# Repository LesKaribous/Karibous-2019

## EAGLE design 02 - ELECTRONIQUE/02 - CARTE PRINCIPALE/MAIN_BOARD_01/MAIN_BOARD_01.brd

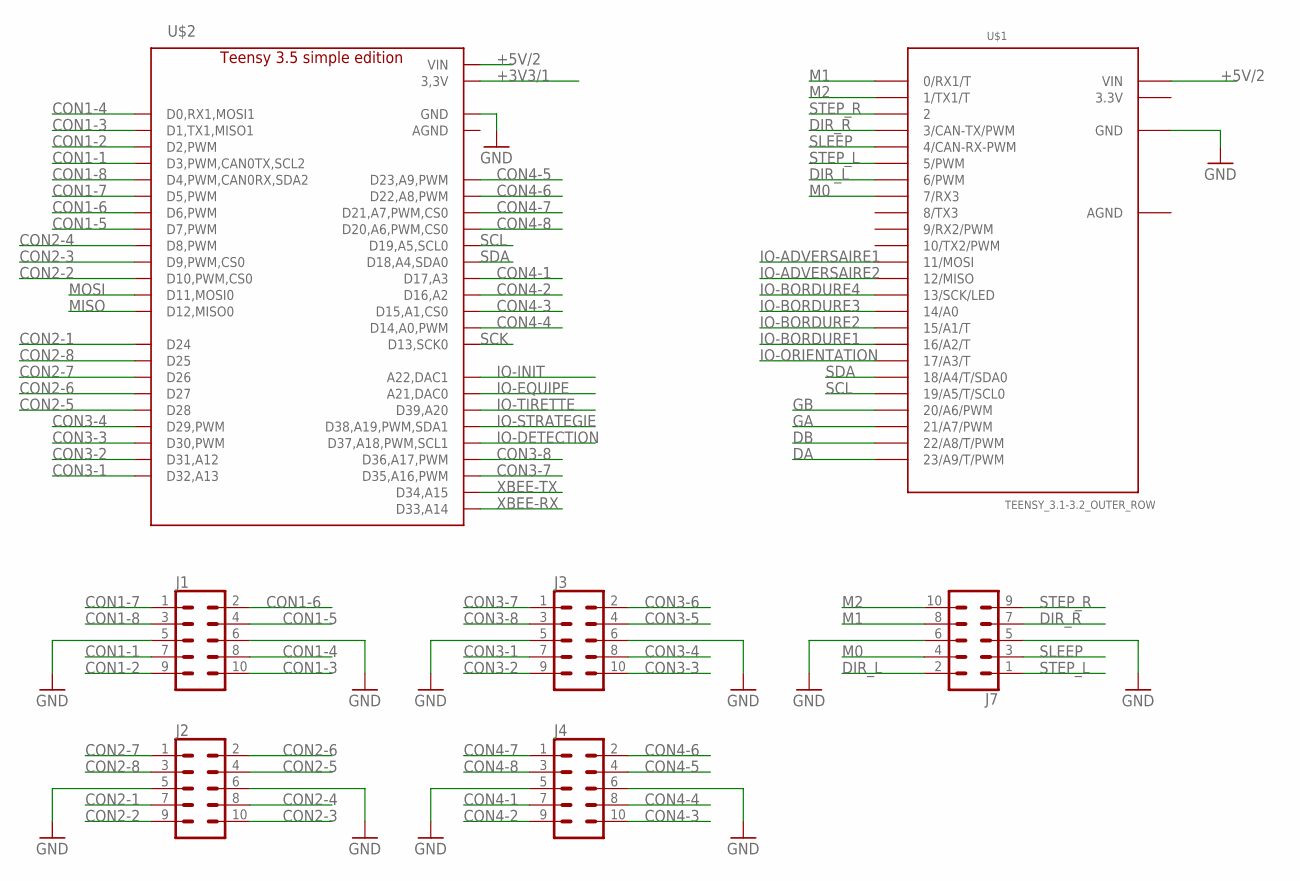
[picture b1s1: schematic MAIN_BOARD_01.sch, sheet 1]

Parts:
J1, J2, J3, J4, J7: CONN_05X2SHD; 2X5-SHROUDED
U$1: TEENSY_3.1-3.2_OUTER_ROW; TEENSY_3.0-3.2&LC_OUTER_ROW
U$2: TEENSY_3.5; TEENSY_3.5_LIGHT

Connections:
3.3V: U$1.3.3V
+3V3/1: U$2.P$15 (3,3V), U$2.P$46 (3,3V); also elsewhere on the board
+5V/2: U$1.V_IN (VIN), U$2.P$48 (VIN); also elsewhere on the board
AGND: U$1.AGND
CON1-1: J1.7, U$2.P$5 (D3,PWM,CAN0TX,SCL2)
CON1-2: J1.9, U$2.P$4 (D2,PWM)
CON1-3: J1.10, U$2.P$3 (D1,TX1,MISO1)
CON1-4: J1.8, U$2.P$2 (D0,RX1,MOSI1)
CON1-5: J1.4, U$2.P$9 (D7,PWM)
CON1-6: J1.2, U$2.P$8 (D6,PWM)
CON1-7: J1.1, U$2.P$7 (D5,PWM)
CON1-8: J1.3, U$2.P$6 (D4,PWM,CAN0RX,SDA2)
CON2-1: J2.7, U$2.P$16 (D24)
CON2-2: J2.9, U$2.P$12 (D10,PWM,CS0)
CON2-3: J2.10, U$2.P$11 (D9,PWM,CS0)
CON2-4: J2.8, U$2.P$10 (D8,PWM)
CON2-5: J2.4, U$2.P$20 (D28)
CON2-6: J2.2, U$2.P$19 (D27)
CON2-7: J2.1, U$2.P$18 (D26)
CON2-8: J2.3, U$2.P$17 (D25)
CON3-1: J3.7, U$2.P$24 (D32,A13)
CON3-2: J3.9, U$2.P$23 (D31,A12)
CON3-3: J3.10, U$2.P$22 (D30,PWM)
CON3-4: J3.8, U$2.P$21 (D29,PWM)
CON3-5: J3.4
CON3-6: J3.2
CON3-7: J3.1, U$2.P$27 (D35,A16,PWM)
CON3-8: J3.3, U$2.P$28 (D36,A17,PWM)
CON4-1: J4.7, U$2.P$39 (D17,A3)
CON4-2: J4.9, U$2.P$38 (D16,A2)
CON4-3: J4.10, U$2.P$37 (D15,A1,CS0)
CON4-4: J4.8, U$2.P$36 (D14,A0,PWM)
CON4-5: J4.4, U$2.P$45 (D23,A9,PWM)
CON4-6: J4.2, U$2.P$44 (D22,A8,PWM)
CON4-7: J4.1, U$2.P$43 (D21,A7,PWM,CS0)
CON4-8: J4.3, U$2.P$42 (D20,A6,PWM,CS0)
DA: U$1.23/A9 (23/A9/T/PWM); also elsewhere on the board
DB: U$1.22/A8 (22/A8/T/PWM); also elsewhere on the board
DIR_L: J7.2, U$1.6 (6/PWM)
DIR_R: J7.7, U$1.3 (3/CAN-TX/PWM)
GA: U$1.21/A7 (21/A7/PWM); also elsewhere on the board
GB: U$1.20/A6 (20/A6/PWM); also elsewhere on the board
GND: J1.5, J1.6, J2.5, J2.6, J3.5, J3.6, J4.5, J4.6, J7.5, J7.6, U$1.GND, U$2.GND, U$2.P$34 (GND); also elsewhere on the board
IO-ADVERSAIRE1: U$1.11 (11/MOSI); also elsewhere on the board
IO-ADVERSAIRE2: U$1.12 (12/MISO); also elsewhere on the board
IO-BORDURE1: U$1.16/A2 (16/A2/T); also elsewhere on the board
IO-BORDURE2: U$1.15/A1 (15/A1/T); also elsewhere on the board
IO-BORDURE3: U$1.14/A0; also elsewhere on the board
IO-BORDURE4: U$1.13 (13/SCK/LED); also elsewhere on the board
IO-DETECTION: U$2.P$29 (D37,A18,PWM,SCL1); also elsewhere on the board
IO-EQUIPE: U$2.P$32 (A21,DAC0); also elsewhere on the board
IO-INIT: U$2.P$33 (A22,DAC1); also elsewhere on the board
IO-ORIENTATION: U$1.17/A3 (17/A3/T); also elsewhere on the board
IO-STRATEGIE: U$2.P$30 (D38,A19,PWM,SDA1); also elsewhere on the board
IO-TIRETTE: U$2.P$31 (D39,A20); also elsewhere on the board
M0: J7.4, U$1.7 (7/RX3)
M1: J7.8, U$1.0 (0/RX1/T)
M2: J7.10, U$1.1 (1/TX1/T)
MISO: U$2.P$14 (D12,MISO0); also elsewhere on the board
MOSI: U$2.P$13 (D11,MOSI0); also elsewhere on the board
SCK: U$2.P$35 (D13,SCK0); also elsewhere on the board
SCL: U$1.19/A5 (19/A5/T/SCL0), U$2.P$41 (D19,A5,SCL0)
SDA: U$1.18/A4 (18/A4/T/SDA0), U$2.P$40 (D18,A4,SDA0)
SLEEP: J7.3, U$1.4 (4/CAN-RX-PWM)
STEP_L: J7.1, U$1.5 (5/PWM)
STEP_R: J7.9, U$1.2
XBEE-RX: U$2.P$25 (D33,A14); also elsewhere on the board
XBEE-TX: U$2.P$26 (D34,A15); also elsewhere on the board

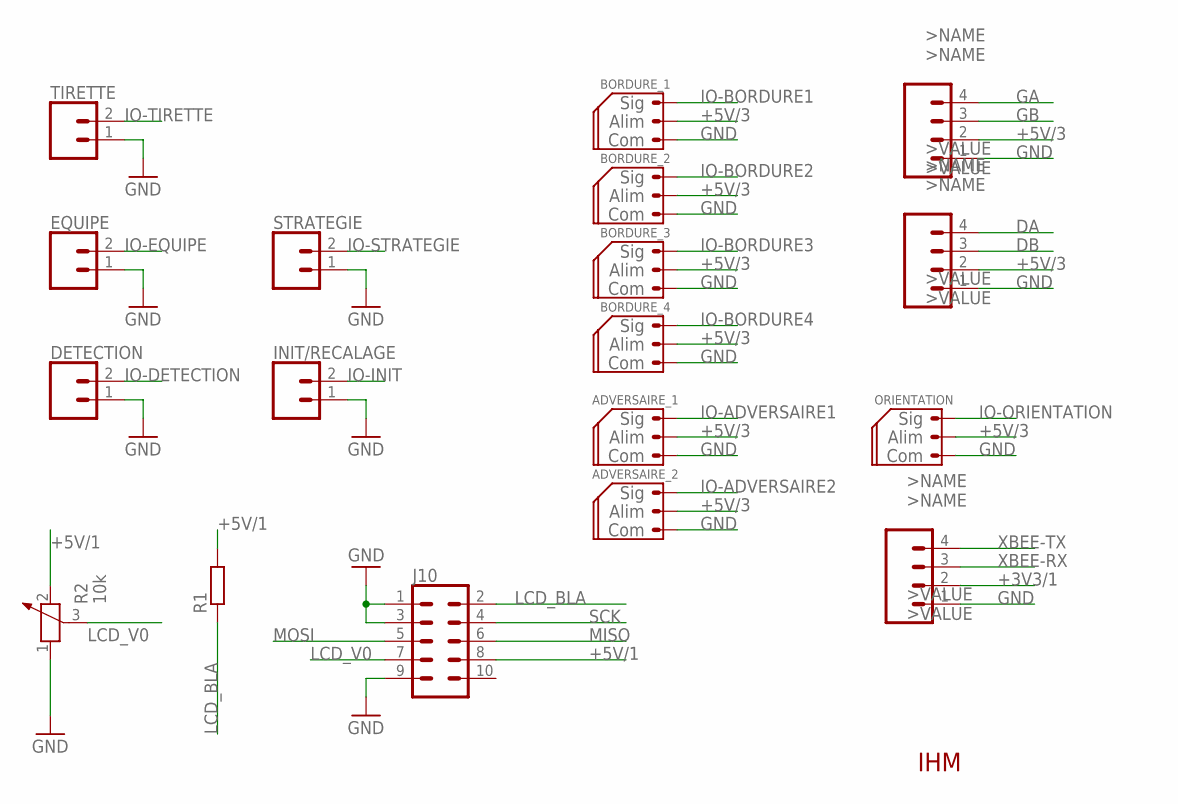
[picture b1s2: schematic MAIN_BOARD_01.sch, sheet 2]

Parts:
ADVERSAIRE_1, ADVERSAIRE_2: CONN_03_SERVO; MOLEX-1X3
BORDURE_1, BORDURE_2, BORDURE_3, BORDURE_4: CONN_03_SERVO; MOLEX-1X3
DETECTION: CONN_02POLAR; MOLEX-1X2
ENC_DROIT, ENC_DROIT1: CONN_04POLAR; MOLEX-1X4
ENC_GAUCHE: CONN_04POLAR; MOLEX-1X4
EQUIPE: CONN_02POLAR; MOLEX-1X2
INIT/RECALAGE: CONN_02POLAR; MOLEX-1X2
J10: CONN_05X2SHD; 2X5-SHROUDED
ORIENTATION: CONN_03_SERVO; MOLEX-1X3
R1: R-EU_R1206; R1206
R2: 10k; PT-10
STRATEGIE: CONN_02POLAR; MOLEX-1X2
TIRETTE: CONN_02POLAR; MOLEX-1X2

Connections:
+3V3/1: ENC_DROIT1.2; also elsewhere on the board
+5V/1: J10.8, R1.2, R2.2; also elsewhere on the board
+5V/3: ADVERSAIRE_1.2, ADVERSAIRE_2.2, BORDURE_1.2, BORDURE_2.2, BORDURE_3.2, BORDURE_4.2, ENC_DROIT.2, ENC_GAUCHE.2, ORIENTATION.2; also elsewhere on the board
DA: ENC_DROIT.4; also elsewhere on the board
DB: ENC_DROIT.3; also elsewhere on the board
GA: ENC_GAUCHE.4; also elsewhere on the board
GB: ENC_GAUCHE.3; also elsewhere on the board
GND: ADVERSAIRE_1.1, ADVERSAIRE_2.1, BORDURE_1.1, BORDURE_2.1, BORDURE_3.1, BORDURE_4.1, DETECTION.1, ENC_DROIT.1, ENC_DROIT1.1, ENC_GAUCHE.1, EQUIPE.1, INIT/RECALAGE.1, J10.1, J10.3, J10.9, ORIENTATION.1, R2.1, STRATEGIE.1, TIRETTE.1; also elsewhere on the board
IO-ADVERSAIRE1: ADVERSAIRE_1.3; also elsewhere on the board
IO-ADVERSAIRE2: ADVERSAIRE_2.3; also elsewhere on the board
IO-BORDURE1: BORDURE_1.3; also elsewhere on the board
IO-BORDURE2: BORDURE_2.3; also elsewhere on the board
IO-BORDURE3: BORDURE_3.3; also elsewhere on the board
IO-BORDURE4: BORDURE_4.3; also elsewhere on the board
IO-DETECTION: DETECTION.2; also elsewhere on the board
IO-EQUIPE: EQUIPE.2; also elsewhere on the board
IO-INIT: INIT/RECALAGE.2; also elsewhere on the board
IO-ORIENTATION: ORIENTATION.3; also elsewhere on the board
IO-STRATEGIE: STRATEGIE.2; also elsewhere on the board
IO-TIRETTE: TIRETTE.2; also elsewhere on the board
LCD_BLA: J10.2, R1.1
LCD_V0: J10.7, R2.3
MISO: J10.6; also elsewhere on the board
MOSI: J10.5; also elsewhere on the board
SCK: J10.4; also elsewhere on the board
XBEE-RX: ENC_DROIT1.3; also elsewhere on the board
XBEE-TX: ENC_DROIT1.4; also elsewhere on the board

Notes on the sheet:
IHM

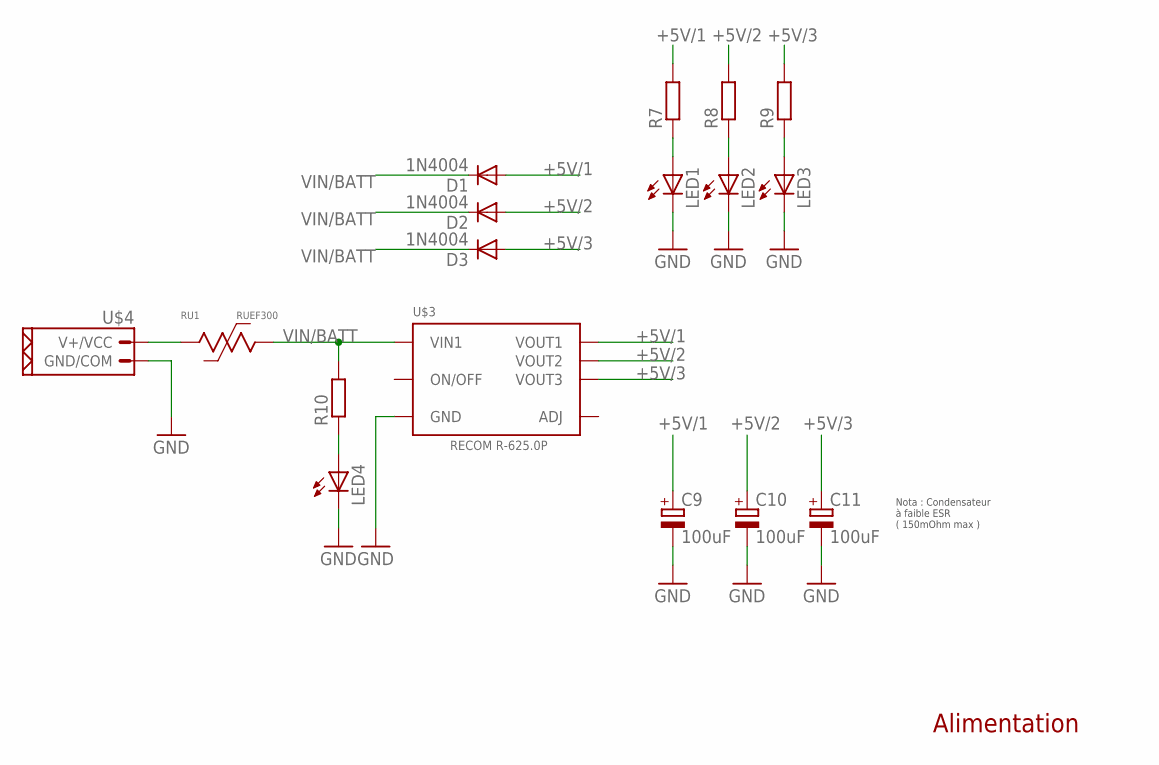
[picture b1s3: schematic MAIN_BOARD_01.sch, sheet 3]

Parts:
C9, C10, C11: 100uF; E5-10,5
D1, D2, D3: 1N4004; DO41-10
LED1, LED2, LED3, LED4: LED_E; LED_1206
R7, R8, R9, R10: R-EU_R1206; R1206
RU1: RUEF300
U$3: R-625.0P; R-6XXXP
U$4: CONN_02_PUI; NSK396-2C

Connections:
+5V/1: C9.+, D1.A, R7.2, U$3.P$9 (VOUT1); also elsewhere on the board
+5V/2: C10.+, D2.A, R8.2, U$3.P$10 (VOUT2); also elsewhere on the board
+5V/3: C11.+, D3.A, R9.2, U$3.P$11 (VOUT3); also elsewhere on the board
ADJ: U$3.P$12 (ADJ)
GND: C9.-, C10.-, C11.-, LED1.C, LED2.C, LED3.C, LED4.C, U$3.P$5 (GND), U$3.P$6 (GND), U$3.P$7 (GND), U$3.P$8 (GND), U$4.P$1 (GND/COM); also elsewhere on the board
unnamed: LED1.A, R7.1
unnamed: LED4.A, R10.1
unnamed: RU1.P$1, U$4.P$2 (V+/VCC)
unnamed: LED2.A, R8.1
unnamed: LED3.A, R9.1
VIN/BATT: D1.C, D2.C, D3.C, R10.2, RU1.P$2, U$3.P$2 (VIN1), U$3.P$3 (VIN1), U$3.P$4 (VIN1)

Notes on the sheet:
Nota : Condensateur à faible ESR ( 150mOhm max )
Alimentation

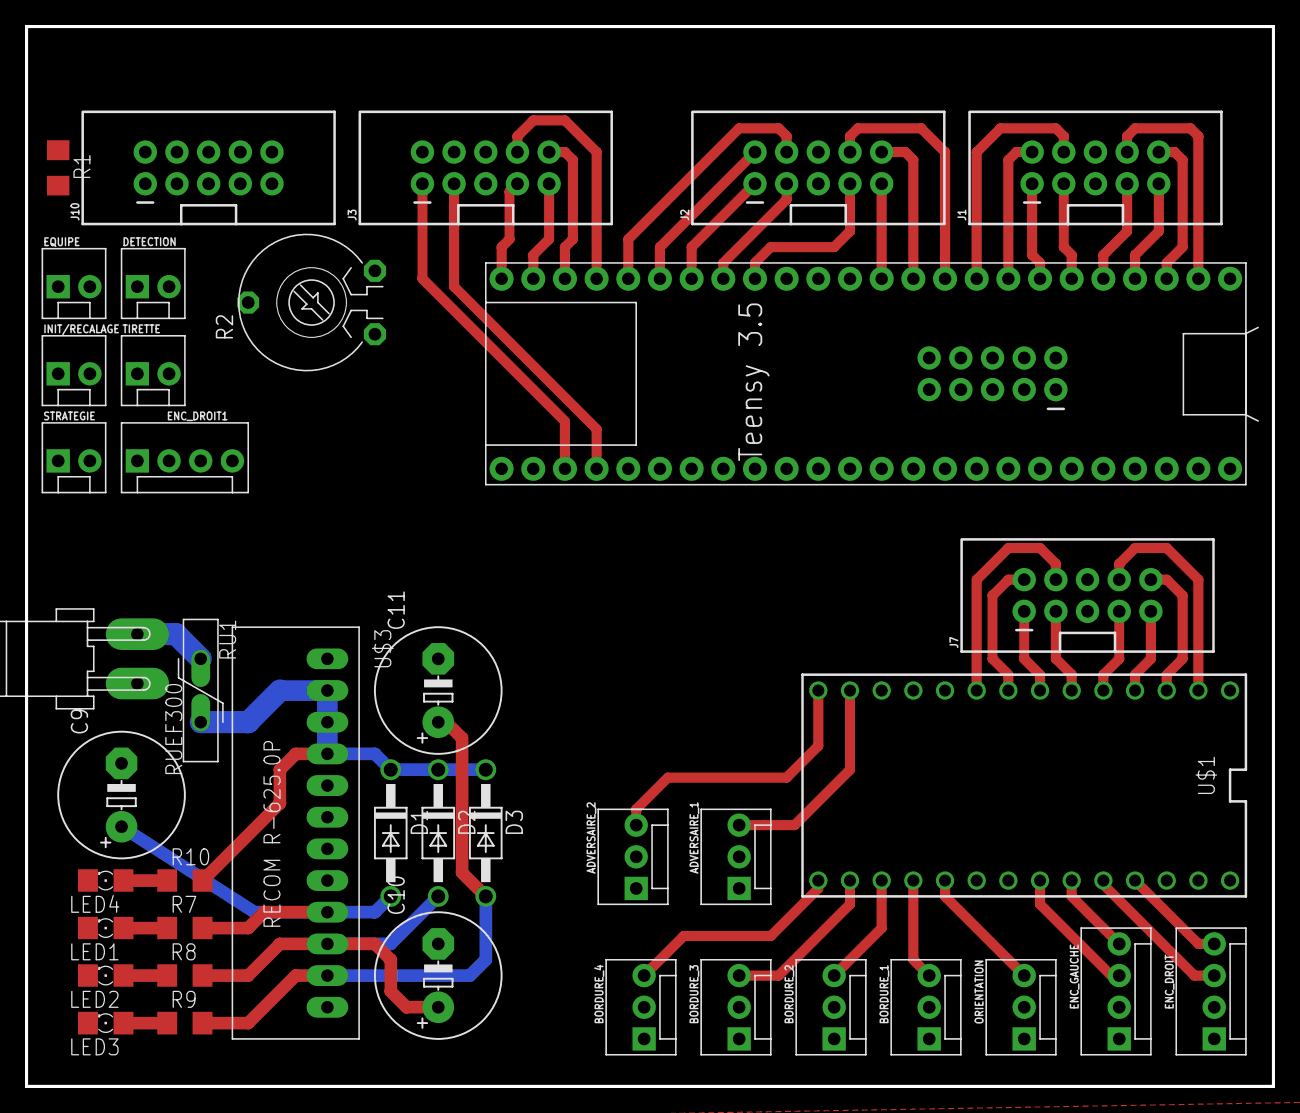
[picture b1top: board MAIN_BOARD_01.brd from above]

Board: 2 copper layers, 100.0 x 85.0 mm, 42 parts (1 on the bottom side), 74 nets.

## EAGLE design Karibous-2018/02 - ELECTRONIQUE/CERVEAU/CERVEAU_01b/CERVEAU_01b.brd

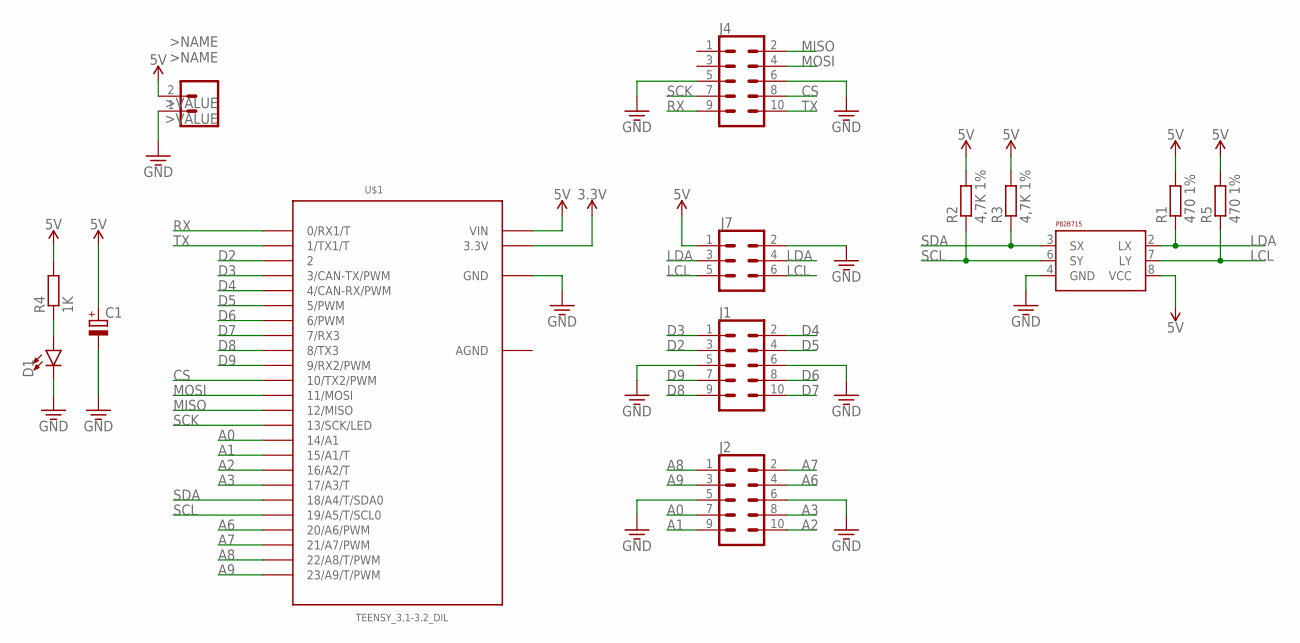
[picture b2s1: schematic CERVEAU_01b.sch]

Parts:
C1: CPOL-EUE2.5-6; E2,5-6
D1: LED5MM; LED_5MM
J1, J2, J4: CONN_05X2SHD; 2X5-SHROUDED
J3: CONN_02POLAR; MOLEX-1X2
J7: CONN_03X2SHROUD; 2X3-SHROUDED
R1, R5: 470 1%; 0207/2V
R2, R3: 4,7K 1%; 0207/2V
R4: 1K; 0207/2V
U$1: TEENSY_3.1-3.2_DIL; TEENSY_3.0-3.2&LC_DIL
U$2: P82B715; SOCKET-08

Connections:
3.3V: U$1.3.3V
5V: C1.+, J3.2, J7.1, R1.2, R2.2, R3.2, R4.2, R5.2, U$1.VIN, U$2.8 (VCC)
A0: J2.7, U$1.14/A0 (14/A1)
A1: J2.9, U$1.15/A1 (15/A1/T)
A2: J2.10, U$1.16/A2 (16/A2/T)
A3: J2.8, U$1.17/A3 (17/A3/T)
A6: J2.4, U$1.20/A6 (20/A6/PWM)
A7: J2.2, U$1.21/A7 (21/A7/PWM)
A8: J2.1, U$1.22/A8 (22/A8/T/PWM)
A9: J2.3, U$1.23/A9 (23/A9/T/PWM)
AGND: U$1.AGND
CS: J4.8, U$1.10 (10/TX2/PWM)
D2: J1.3, U$1.2
D3: J1.1, U$1.3 (3/CAN-TX/PWM)
D4: J1.2, U$1.4 (4/CAN-RX/PWM)
D5: J1.4, U$1.5 (5/PWM)
D6: J1.8, U$1.6 (6/PWM)
D7: J1.10, U$1.7 (7/RX3)
D8: J1.9, U$1.8 (8/TX3)
D9: J1.7, U$1.9 (9/RX2/PWM)
GND: C1.-, D1.K (C), J1.5, J1.6, J2.5, J2.6, J3.1, J4.5, J4.6, J7.2, U$1.GND, U$2.4 (GND)
LCL: J7.5, J7.6, R5.1, U$2.7 (LY)
LDA: J7.3, J7.4, R1.1, U$2.2 (LX)
MISO: J4.2, U$1.12 (12/MISO)
MOSI: J4.4, U$1.11 (11/MOSI)
unnamed: D1.A, R4.1
RX: J4.9, U$1.0 (0/RX1/T)
SCK: J4.7, U$1.13 (13/SCK/LED)
SCL: R2.1, U$1.19/A5 (19/A5/T/SCL0), U$2.6 (SY)
SDA: R3.1, U$1.18/A4 (18/A4/T/SDA0), U$2.3 (SX)
TX: J4.10, U$1.1 (1/TX1/T)

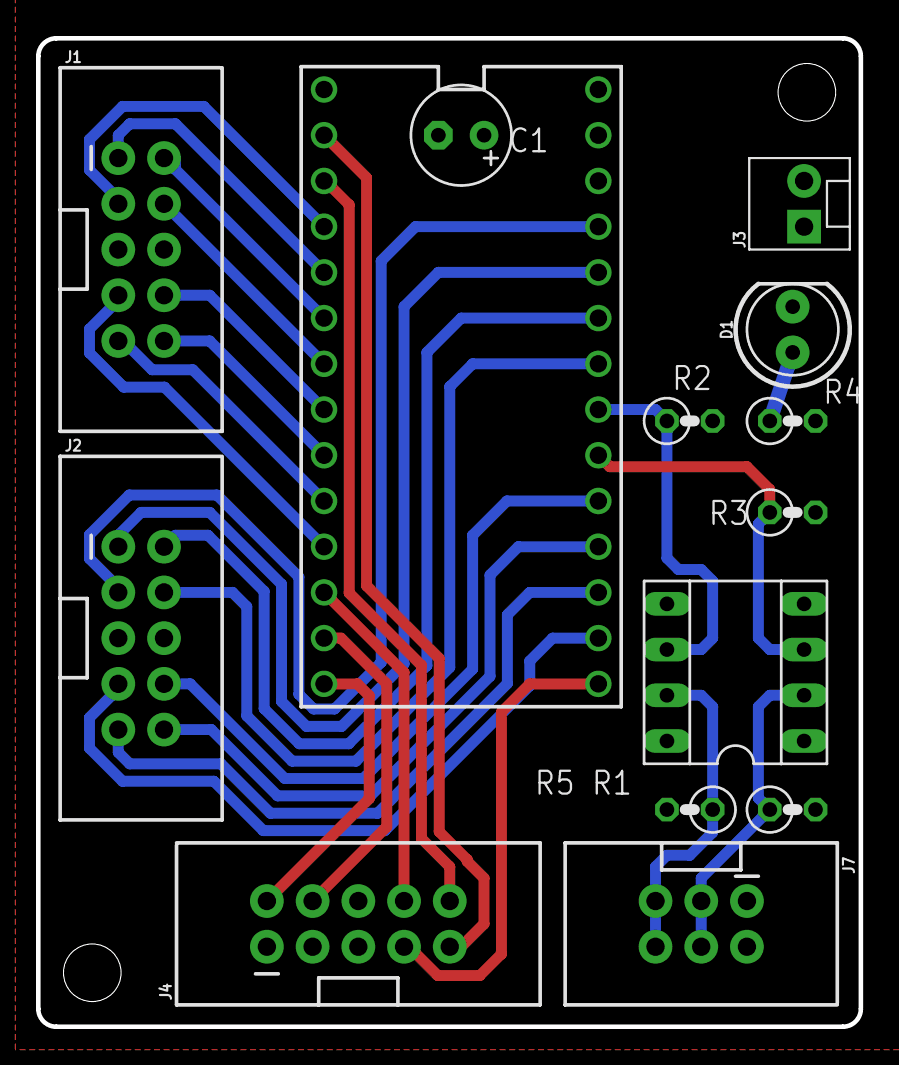
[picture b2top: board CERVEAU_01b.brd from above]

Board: 2 copper layers, 45.7 x 54.9 mm, 14 parts (0 on the bottom side), 29 nets.

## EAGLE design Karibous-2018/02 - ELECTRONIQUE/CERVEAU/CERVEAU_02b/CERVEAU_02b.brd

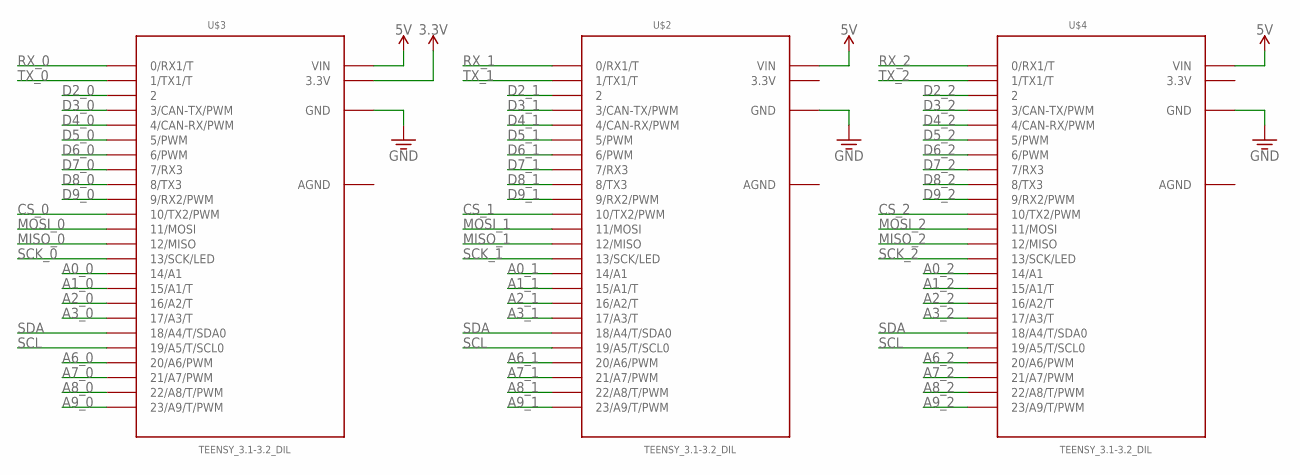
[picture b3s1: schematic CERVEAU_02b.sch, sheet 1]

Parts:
U$2, U$3, U$4: TEENSY_3.1-3.2_DIL; TEENSY_3.0-3.2&LC_DIL

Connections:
3.3V: U$3.3.3V; also elsewhere on the board
5V: U$2.VIN, U$3.VIN, U$4.VIN; also elsewhere on the board
A0_0: U$3.14/A0 (14/A1); also elsewhere on the board
A0_1: U$2.14/A0 (14/A1); also elsewhere on the board
A0_2: U$4.14/A0 (14/A1); also elsewhere on the board
A1_0: U$3.15/A1 (15/A1/T); also elsewhere on the board
A1_1: U$2.15/A1 (15/A1/T); also elsewhere on the board
A1_2: U$4.15/A1 (15/A1/T); also elsewhere on the board
A2_0: U$3.16/A2 (16/A2/T); also elsewhere on the board
A2_1: U$2.16/A2 (16/A2/T); also elsewhere on the board
A2_2: U$4.16/A2 (16/A2/T); also elsewhere on the board
A3_0: U$3.17/A3 (17/A3/T); also elsewhere on the board
A3_1: U$2.17/A3 (17/A3/T); also elsewhere on the board
A3_2: U$4.17/A3 (17/A3/T); also elsewhere on the board
A6_0: U$3.20/A6 (20/A6/PWM); also elsewhere on the board
A6_1: U$2.20/A6 (20/A6/PWM); also elsewhere on the board
A6_2: U$4.20/A6 (20/A6/PWM); also elsewhere on the board
A7_0: U$3.21/A7 (21/A7/PWM); also elsewhere on the board
A7_1: U$2.21/A7 (21/A7/PWM); also elsewhere on the board
A7_2: U$4.21/A7 (21/A7/PWM); also elsewhere on the board
A8_0: U$3.22/A8 (22/A8/T/PWM); also elsewhere on the board
A8_1: U$2.22/A8 (22/A8/T/PWM); also elsewhere on the board
A8_2: U$4.22/A8 (22/A8/T/PWM); also elsewhere on the board
A9_0: U$3.23/A9 (23/A9/T/PWM); also elsewhere on the board
A9_1: U$2.23/A9 (23/A9/T/PWM); also elsewhere on the board
A9_2: U$4.23/A9 (23/A9/T/PWM); also elsewhere on the board
AGND: U$2.AGND, U$3.AGND, U$4.AGND
CS_0: U$3.10 (10/TX2/PWM); also elsewhere on the board
CS_1: U$2.10 (10/TX2/PWM); also elsewhere on the board
CS_2: U$4.10 (10/TX2/PWM); also elsewhere on the board
D2_0: U$3.2; also elsewhere on the board
D2_1: U$2.2; also elsewhere on the board
D2_2: U$4.2; also elsewhere on the board
D3_0: U$3.3 (3/CAN-TX/PWM); also elsewhere on the board
D3_1: U$2.3 (3/CAN-TX/PWM); also elsewhere on the board
D3_2: U$4.3 (3/CAN-TX/PWM); also elsewhere on the board
D4_0: U$3.4 (4/CAN-RX/PWM); also elsewhere on the board
D4_1: U$2.4 (4/CAN-RX/PWM); also elsewhere on the board
D4_2: U$4.4 (4/CAN-RX/PWM); also elsewhere on the board
D5_0: U$3.5 (5/PWM); also elsewhere on the board
D5_1: U$2.5 (5/PWM); also elsewhere on the board
D5_2: U$4.5 (5/PWM); also elsewhere on the board
D6_0: U$3.6 (6/PWM); also elsewhere on the board
D6_1: U$2.6 (6/PWM); also elsewhere on the board
D6_2: U$4.6 (6/PWM); also elsewhere on the board
D7_0: U$3.7 (7/RX3); also elsewhere on the board
D7_1: U$2.7 (7/RX3); also elsewhere on the board
D7_2: U$4.7 (7/RX3); also elsewhere on the board
D8_0: U$3.8 (8/TX3); also elsewhere on the board
D8_1: U$2.8 (8/TX3); also elsewhere on the board
D8_2: U$4.8 (8/TX3); also elsewhere on the board
D9_0: U$3.9 (9/RX2/PWM); also elsewhere on the board
D9_1: U$2.9 (9/RX2/PWM); also elsewhere on the board
D9_2: U$4.9 (9/RX2/PWM); also elsewhere on the board
GND: U$2.3.3V, U$2.GND, U$3.GND, U$4.3.3V, U$4.GND; also elsewhere on the board
MISO_0: U$3.12 (12/MISO); also elsewhere on the board
MISO_1: U$2.12 (12/MISO); also elsewhere on the board
MISO_2: U$4.12 (12/MISO); also elsewhere on the board
MOSI_0: U$3.11 (11/MOSI); also elsewhere on the board
MOSI_1: U$2.11 (11/MOSI); also elsewhere on the board
MOSI_2: U$4.11 (11/MOSI); also elsewhere on the board
RX_0: U$3.0 (0/RX1/T); also elsewhere on the board
RX_1: U$2.0 (0/RX1/T); also elsewhere on the board
RX_2: U$4.0 (0/RX1/T); also elsewhere on the board
SCK_0: U$3.13 (13/SCK/LED); also elsewhere on the board
SCK_1: U$2.13 (13/SCK/LED); also elsewhere on the board
SCK_2: U$4.13 (13/SCK/LED); also elsewhere on the board
SCL: U$2.19/A5 (19/A5/T/SCL0), U$3.19/A5 (19/A5/T/SCL0), U$4.19/A5 (19/A5/T/SCL0); also elsewhere on the board
SDA: U$2.18/A4 (18/A4/T/SDA0), U$3.18/A4 (18/A4/T/SDA0), U$4.18/A4 (18/A4/T/SDA0); also elsewhere on the board
TX_0: U$3.1 (1/TX1/T); also elsewhere on the board
TX_1: U$2.1 (1/TX1/T); also elsewhere on the board
TX_2: U$4.1 (1/TX1/T); also elsewhere on the board

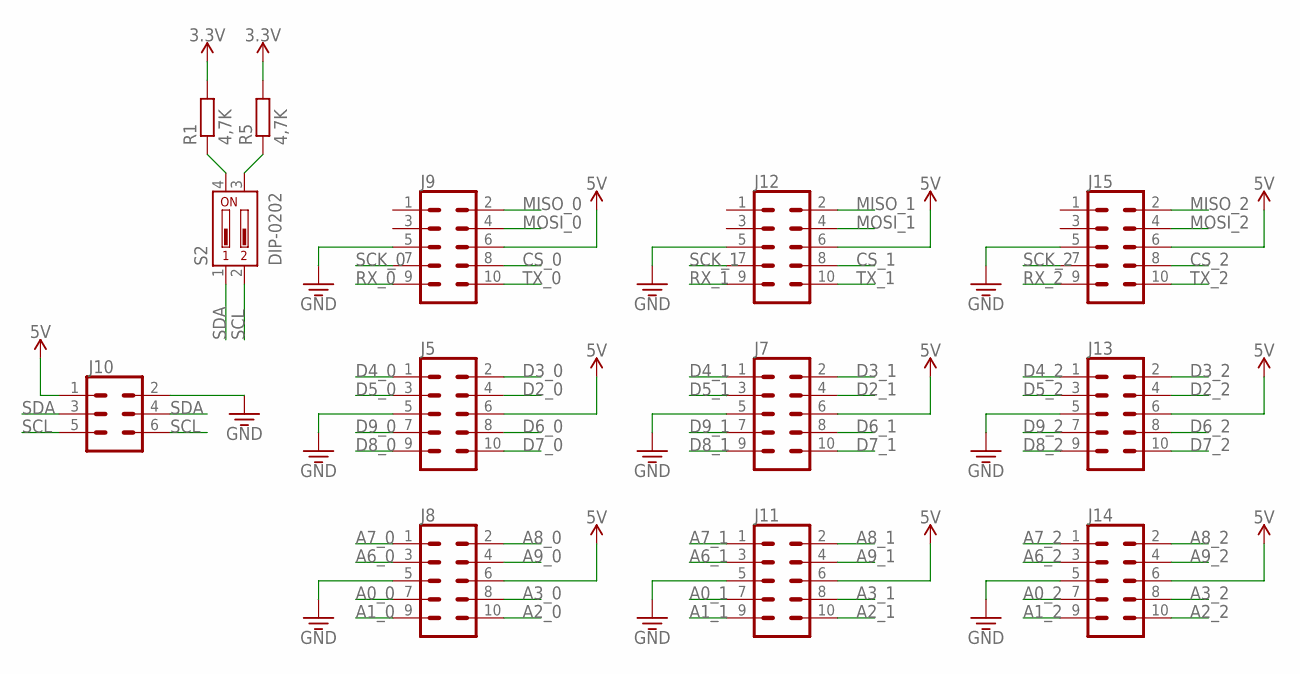
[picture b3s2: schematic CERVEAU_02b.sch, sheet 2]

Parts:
J5, J7, J8, J9, J11, J12, J13, J14, J15: CONN_05X2SHD; 2X5-SHROUDED
J10: CONN_03X2SHROUD; 2X3-SHROUDED
R1, R5: 4,7K; 0207/10
S2: DIP-0202; DIPSWITCH-02

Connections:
3.3V: R1.2, R5.2; also elsewhere on the board
5V: J5.6, J7.6, J8.6, J9.6, J10.1, J11.6, J12.6, J13.6, J14.6, J15.6; also elsewhere on the board
A0_0: J8.7; also elsewhere on the board
A0_1: J11.7; also elsewhere on the board
A0_2: J14.7; also elsewhere on the board
A1_0: J8.9; also elsewhere on the board
A1_1: J11.9; also elsewhere on the board
A1_2: J14.9; also elsewhere on the board
A2_0: J8.10; also elsewhere on the board
A2_1: J11.10; also elsewhere on the board
A2_2: J14.10; also elsewhere on the board
A3_0: J8.8; also elsewhere on the board
A3_1: J11.8; also elsewhere on the board
A3_2: J14.8; also elsewhere on the board
A6_0: J8.3; also elsewhere on the board
A6_1: J11.3; also elsewhere on the board
A6_2: J14.3; also elsewhere on the board
A7_0: J8.1; also elsewhere on the board
A7_1: J11.1; also elsewhere on the board
A7_2: J14.1; also elsewhere on the board
A8_0: J8.2; also elsewhere on the board
A8_1: J11.2; also elsewhere on the board
A8_2: J14.2; also elsewhere on the board
A9_0: J8.4; also elsewhere on the board
A9_1: J11.4; also elsewhere on the board
A9_2: J14.4; also elsewhere on the board
CS_0: J9.8; also elsewhere on the board
CS_1: J12.8; also elsewhere on the board
CS_2: J15.8; also elsewhere on the board
D2_0: J5.4; also elsewhere on the board
D2_1: J7.4; also elsewhere on the board
D2_2: J13.4; also elsewhere on the board
D3_0: J5.2; also elsewhere on the board
D3_1: J7.2; also elsewhere on the board
D3_2: J13.2; also elsewhere on the board
D4_0: J5.1; also elsewhere on the board
D4_1: J7.1; also elsewhere on the board
D4_2: J13.1; also elsewhere on the board
D5_0: J5.3; also elsewhere on the board
D5_1: J7.3; also elsewhere on the board
D5_2: J13.3; also elsewhere on the board
D6_0: J5.8; also elsewhere on the board
D6_1: J7.8; also elsewhere on the board
D6_2: J13.8; also elsewhere on the board
D7_0: J5.10; also elsewhere on the board
D7_1: J7.10; also elsewhere on the board
D7_2: J13.10; also elsewhere on the board
D8_0: J5.9; also elsewhere on the board
D8_1: J7.9; also elsewhere on the board
D8_2: J13.9; also elsewhere on the board
D9_0: J5.7; also elsewhere on the board
D9_1: J7.7; also elsewhere on the board
D9_2: J13.7; also elsewhere on the board
GND: J5.5, J7.5, J8.5, J9.5, J10.2, J11.5, J12.5, J13.5, J14.5, J15.5; also elsewhere on the board
MISO_0: J9.2; also elsewhere on the board
MISO_1: J12.2; also elsewhere on the board
MISO_2: J15.2; also elsewhere on the board
MOSI_0: J9.4; also elsewhere on the board
MOSI_1: J12.4; also elsewhere on the board
MOSI_2: J15.4; also elsewhere on the board
unnamed: R1.1, S2.4
unnamed: R5.1, S2.3
RX_0: J9.9; also elsewhere on the board
RX_1: J12.9; also elsewhere on the board
RX_2: J15.9; also elsewhere on the board
SCK_0: J9.7; also elsewhere on the board
SCK_1: J12.7; also elsewhere on the board
SCK_2: J15.7; also elsewhere on the board
SCL: J10.5, J10.6, S2.2; also elsewhere on the board
SDA: J10.3, J10.4, S2.1; also elsewhere on the board
TX_0: J9.10; also elsewhere on the board
TX_1: J12.10; also elsewhere on the board
TX_2: J15.10; also elsewhere on the board

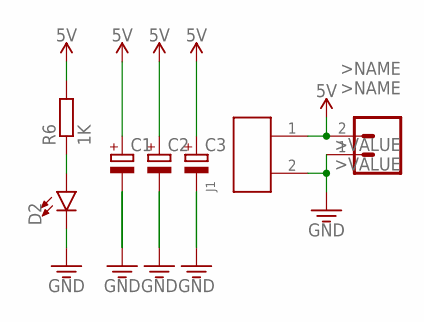
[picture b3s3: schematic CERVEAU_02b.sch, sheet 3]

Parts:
C1, C2, C3: CPOL-EUE2.5-6; E2,5-6
D2: LED5MM; LED_5MM
J1: 645002114822
J2: CONN_02POLAR; MOLEX-1X2
R6: 1K; 0207/10

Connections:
5V: C1.+, C2.+, C3.+, J1.1, J2.2, R6.2; also elsewhere on the board
GND: C1.-, C2.-, C3.-, D2.K (C), J1.2, J2.1; also elsewhere on the board
unnamed: D2.A, R6.1

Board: 2 copper layers, 23 parts (0 on the bottom side), 75 nets, no tracks yet.

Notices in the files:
parts and their libraries:
SparkFun-PowerSymbols: Licensing: Creative Commons ShareAlike 4.0 International - https://creativecommons.org/licenses/by-sa/4.0
Wurth_Elektronik_Electromechanic_Wire_to: Copyright: Würth Elektronik
